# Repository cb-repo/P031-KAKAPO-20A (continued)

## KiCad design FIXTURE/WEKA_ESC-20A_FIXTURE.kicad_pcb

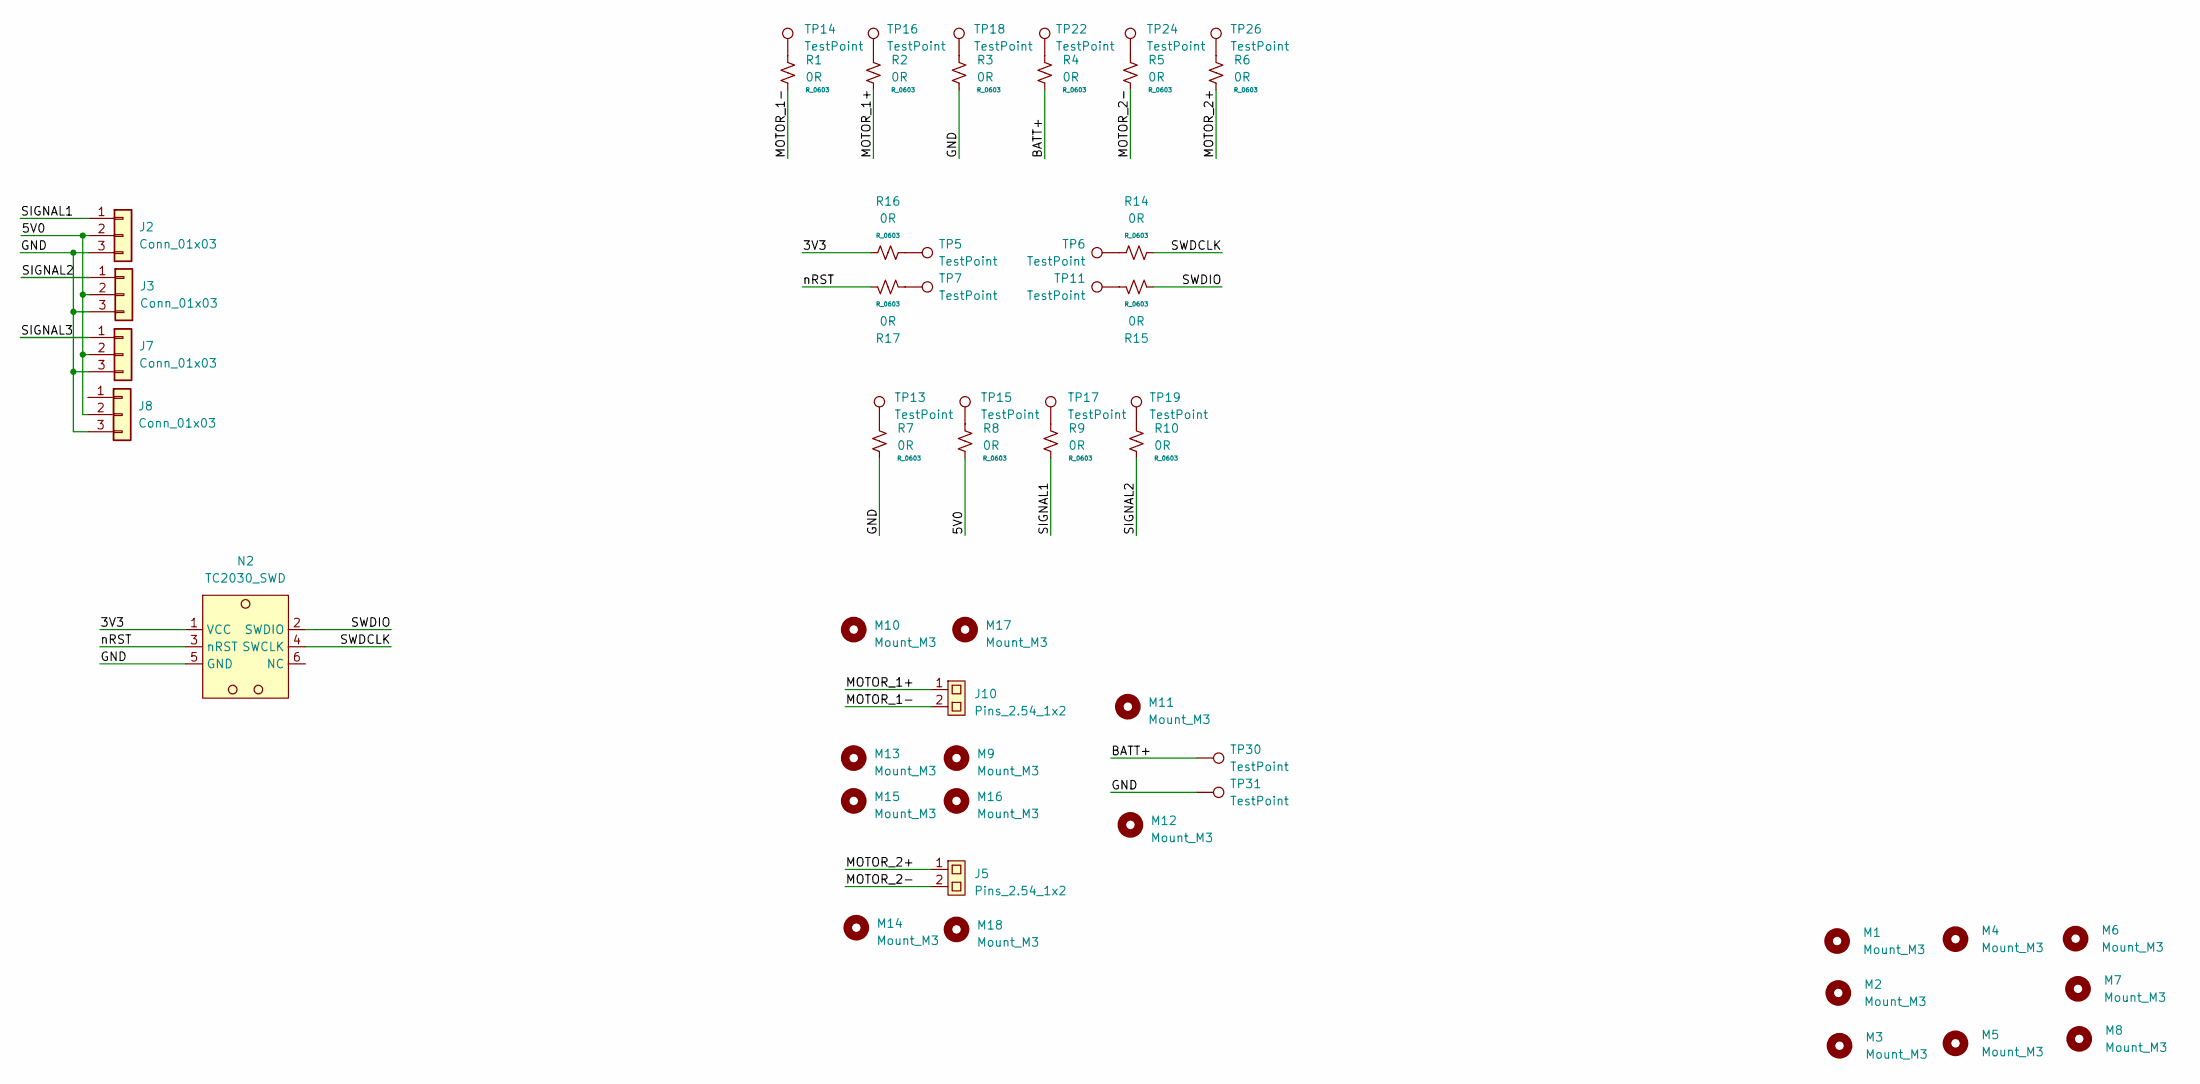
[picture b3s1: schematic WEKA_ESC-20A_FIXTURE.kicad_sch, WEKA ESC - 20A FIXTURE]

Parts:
J2, J3, J7, J8: Conn_01x03; PinHeader_1x03_P2.54mm_Vertical
J5, J10: Pins_2.54_1x2; Pins-2.54-1x2
M1, M2, M3, M4, M5, M6, M7, M8, M9, M10, M11, M12, M13, M14, M15, M16, M17, M18: Mount_M3
N2: TC2030_SWD; TagConnect_TC2030
R1, R2, R3, R4, R5, R6, R7, R8, R9, R10, R14, R15, R16, R17: 0R; R_0603
TP5, TP6, TP7, TP11, TP13, TP14, TP15, TP16, TP17, TP18, TP19, TP22, TP24, TP26, TP30, TP31: TestPoint; TestPoint_THTPad_D3.0mm_Drill1.5mm

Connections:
/3V3: N2.1 (VCC), R16.1
/5V0: J2.2, J3.2, J7.2, J8.2, R8.2
/BATT+: R4.2, TP30.1
/GND: J2.3, J3.3, J7.3, J8.3, N2.5 (GND), R3.2, R7.2, TP31.1
/MOTOR_1+: J10.1, R2.2
/MOTOR_1-: J10.2, R1.2
/MOTOR_2+: J5.1, R6.2
/MOTOR_2-: J5.2, R5.2
/SIGNAL1: J2.1, R9.2
/SIGNAL2: J3.1, R10.2
/SIGNAL3: J7.1
/SWDCLK: N2.4 (SWCLK), R14.2
/SWDIO: N2.2 (SWDIO), R15.2
/nRST: N2.3 (nRST), R17.1
unnamed: R1.1, TP14.1
unnamed: R2.1, TP16.1
unnamed: R3.1, TP18.1
unnamed: R4.1, TP22.1
unnamed: R5.1, TP24.1
unnamed: R6.1, TP26.1
unnamed: R7.1, TP13.1
unnamed: R8.1, TP15.1
unnamed: R9.1, TP17.1
unnamed: R10.1, TP19.1
unnamed: R14.1, TP6.1
unnamed: R15.1, TP11.1
unnamed: R16.2, TP5.1
unnamed: R17.2, TP7.1

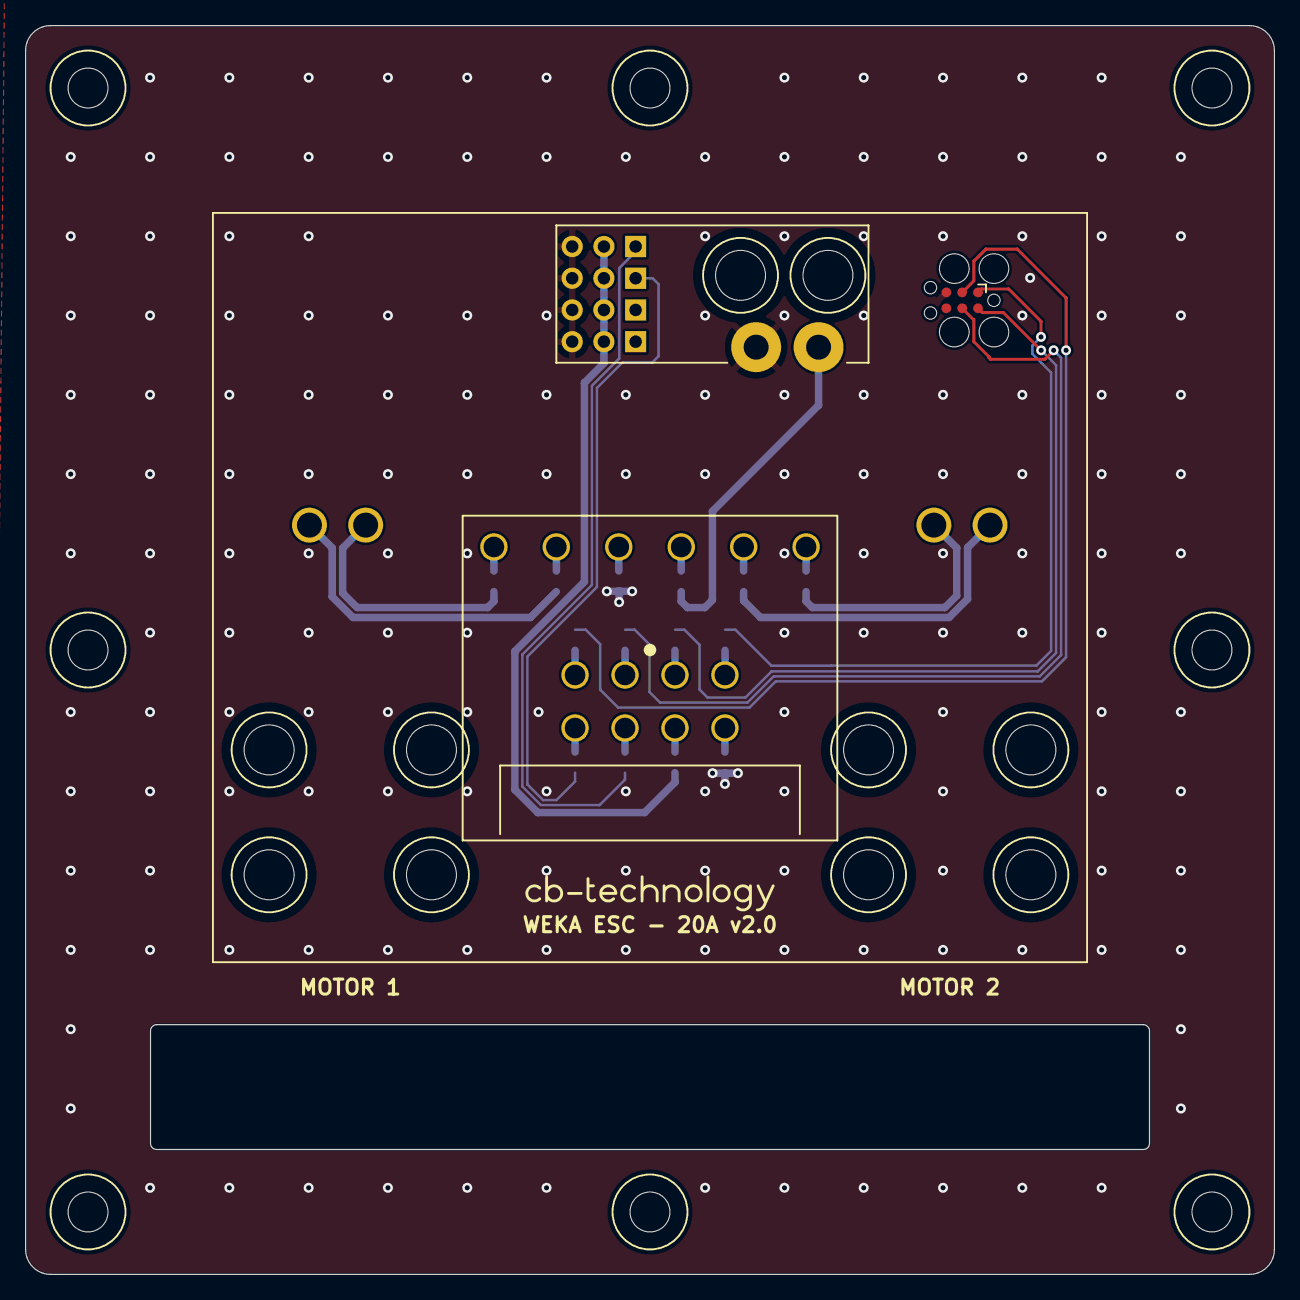
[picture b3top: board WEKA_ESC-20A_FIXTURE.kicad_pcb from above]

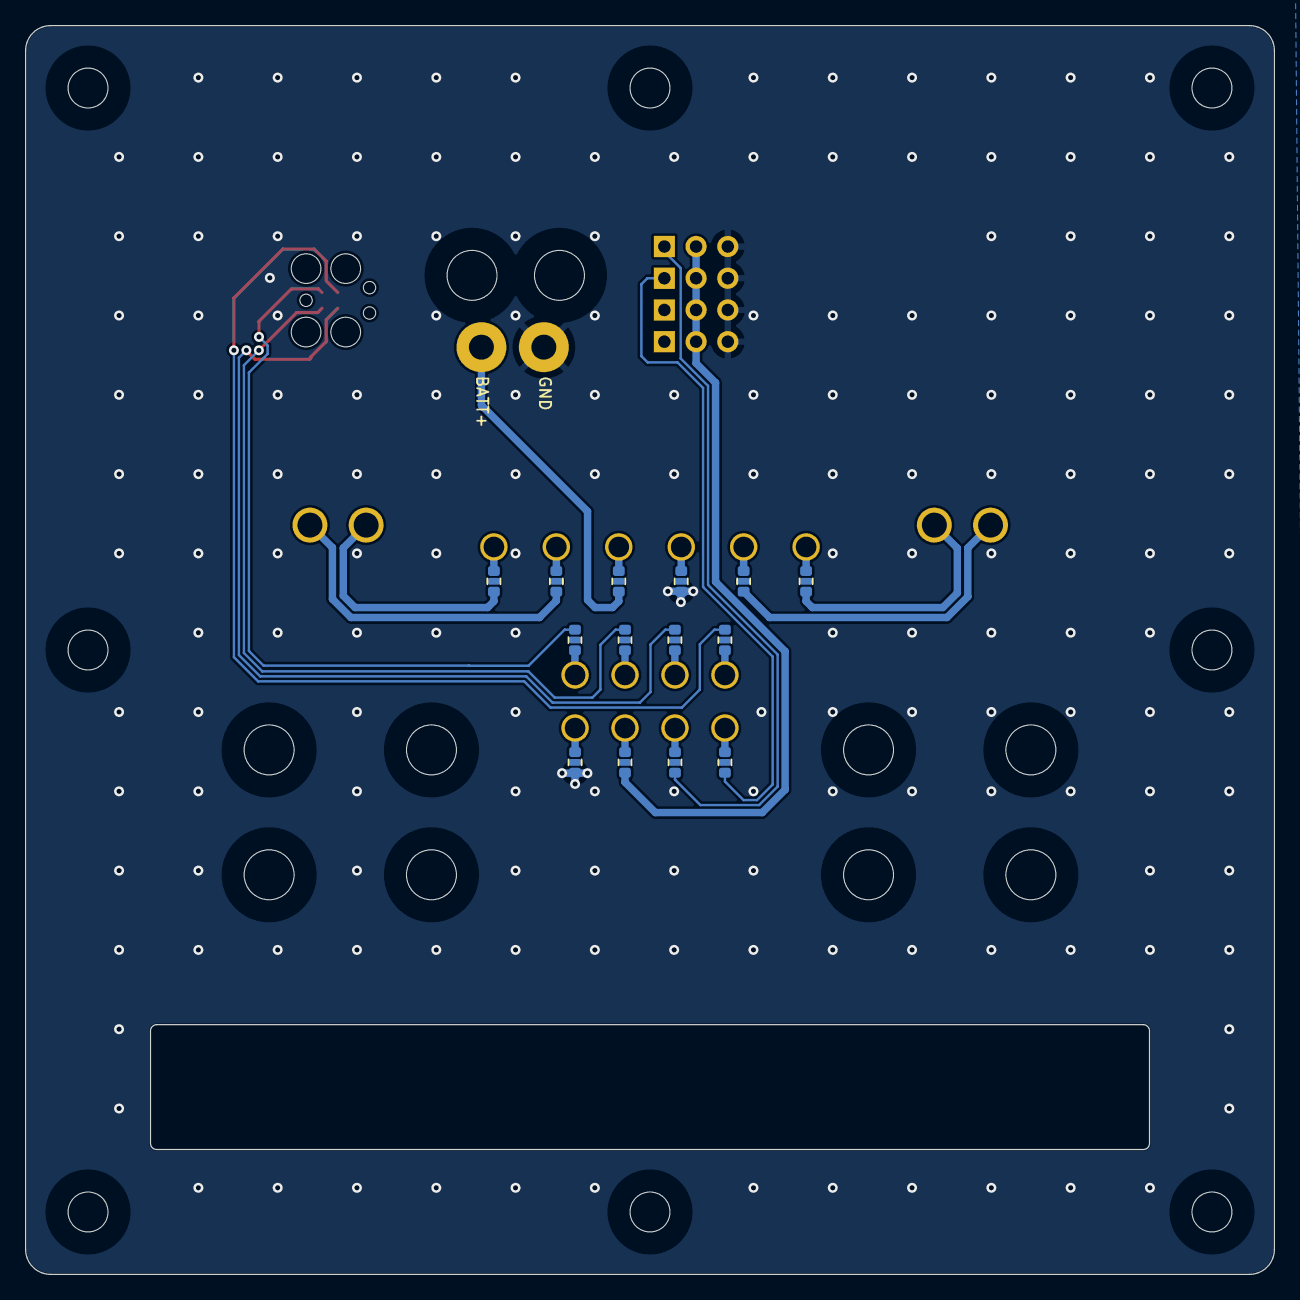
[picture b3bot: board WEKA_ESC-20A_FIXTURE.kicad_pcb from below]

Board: 2 copper layers, 100.0 x 100.0 mm, 55 parts (16 on the bottom side), 27 nets.

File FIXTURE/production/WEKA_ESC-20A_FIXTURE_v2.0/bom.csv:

Designator,Footprint,Quantity,Value,LCSC Part #
"J10, J5",Pins-2.54-1x2,2,Pins_2.54_1x2,
"J2, J3, J7, J8",PinHeader_1x03_P2.54mm_Vertical,4,Conn_01x03,
"R1, R10, R14, R15, R16, R17, R2, R3, R4, R5, R6, R7, R8, R9",R_0603,14,0R,
"TP11, TP13, TP14, TP15, TP16, TP17, TP18, TP19, TP22, TP24, TP26, TP30, TP31, TP5, TP6, TP7",TestPoint_THTPad_D3.0mm_Drill1.5mm,16,TestPoint,

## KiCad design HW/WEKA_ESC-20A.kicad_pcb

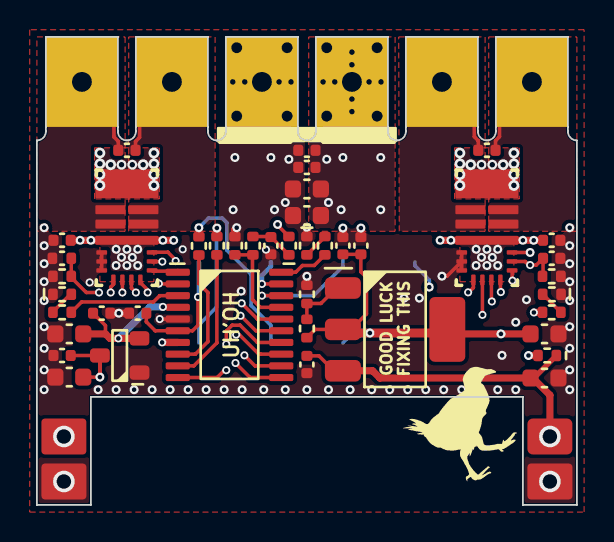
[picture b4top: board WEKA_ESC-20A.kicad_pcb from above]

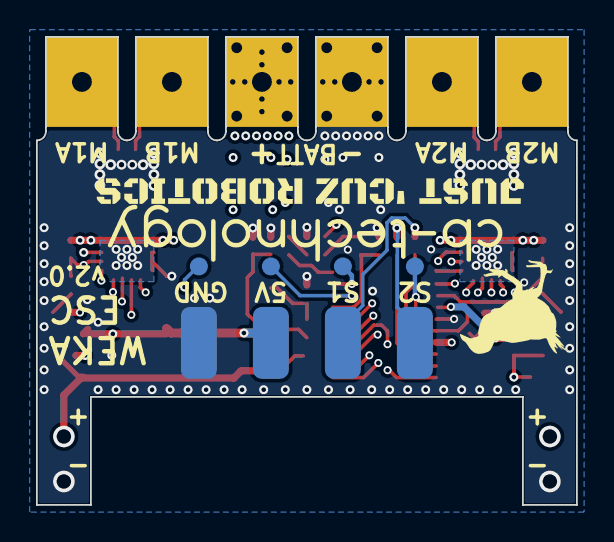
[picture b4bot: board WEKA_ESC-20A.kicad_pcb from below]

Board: 4 copper layers, 30.0 x 26.0 mm, 60 parts (13 on the bottom side), 34 nets.

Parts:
C1: 1uF 35V; C_0402
C2, C3, C4, C6, C7, C8, C10, C14, C19, C20, C23, C28, C29: 100nF 50V; C_0402
C5, C12, C15: 10uF 10V; C_0603
C9, C16, C17: 10uF 35V; C_0603
C11: 1uF 50V; C_0402
D1, D2: RB161QS-40T18R; R_0402
DS1, DS3: BLUE; DS_0402
DS2: RED; DS_0402
N1, N2, N3, N4: Pad_4x2
N5, N6, N7, N8: Pad_4x2_TH; Pad_4x2
N11, N12, N13, N14, N15, N16: Finger_4x5_M1
R1, R3: 619R 1%; R_0402
R2: 243 1%; R_0402
R6, R7: 1K 1%; R_0402
R10, R11, R12: 120R 1%; R_0402
R24: 100K 1%; R_0402
R25: 10K 1%; R_0402
R27: 732 1%; R_0402
TP1, TP2, TP3, TP4: TestPoint; TestPoint_Pad_D1.5mm
U1, U2: DRV8244S-Q1; VQFN-HR-16
U3: LR7533-T; SOT23_3
U4: LM317EMPX/NOPB; SOT223_3
U5: STM32C011F4P6; TSSOP20_4.4mm

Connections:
+3V3: C4.1, C5.1, TP1.1, U1.3 (nSLEEP), U2.3 (nSLEEP), U3.2 (VOUT), U5.4 (VDD/VDDA)
+5V: C1.1, C2.1, C10.1, C12.1, C15.1, N5.1, R2.1, U3.3 (VIN), U4.2 (VOUT)
/MCU/SWDCLK: TP4.1, U5.19 (PA14-BOOT0[SWDCLK])
/MCU/SWDIO: TP3.1, U5.18 (PA13[SWDIO])
/MCU/nRST: C14.1, TP2.1, U5.6 (PF2-NRST)
GND: C1.2, C2.2, C3.2, C4.2, C5.2, C6.2, C9.2, C10.2, C11.2, C12.2, C14.2, C15.2, C16.2, C17.2, C19.2, C20.2, C23.2, C28.2, C29.2, DS1.1 (K), DS2.1 (K), DS3.1 (K), N2.1, N4.1, N6.1, N12.1, R1.2, R3.2, R25.2, R27.2, U1.7 (GND), U1.10 (DRVOFF), U1.11 (EN/IN1), U1.12 (PH/IN2), U2.7 (GND), U2.10 (DRVOFF), U2.11 (EN/IN1), U2.12 (PH/IN2), U3.1 (GND), U5.5 (VSS/VSSA)
LED_M1: R11.1, U5.10 (PA3)
LED_M2: R12.1, U5.3 (PC15/OSCX_OUT)
LED_PWR: R10.1, U5.20 (PB6)
MOTOR_A+: C7.1, N13.1, U1.8 (OUT1), U1.9 (OUT1)
MOTOR_A-: C7.2, N14.1, U1.5 (OUT2), U1.6 (OUT2)
MOTOR_A_SNS: C28.1, R1.1, U1.2 (IPROPI), U5.11 (PA4)
MOTOR_A_nFAULT: U1.1 (nFAULT), U5.16 (PA11[PA9])
MOTOR_A_nSCS: U1.13 (nSCS), U5.15 (PA8)
MOTOR_B+: C8.1, N15.1, U2.8 (OUT1), U2.9 (OUT1)
MOTOR_B-: C8.2, N16.1, U2.5 (OUT2), U2.6 (OUT2)
MOTOR_B_SNS: C19.1, R3.1, U2.2 (IPROPI), U5.7 (PA0)
MOTOR_B_nFAULT: U2.1 (nFAULT), U5.1 (PB7)
MOTOR_B_nSCS: U2.13 (nSCS), U5.2 (PC14/OSCX_IN)
MOTOR_SCLK: U1.14 (SCLK), U2.14 (SCLK), U5.12 (PA5)
MOTOR_SDI: U1.15 (SDI), U2.15 (SDI), U5.14 (PA7)
MOTOR_SDO: U1.16 (SDO), U2.16 (SDO), U5.13 (PA6)
unnamed: C23.1, D2.1, R24.1
unnamed: DS1.2 (A), R12.2
unnamed: DS2.2 (A), R10.2
unnamed: DS3.2 (A), R11.2
unnamed: N7.1, R6.1
unnamed: N8.1, R7.1
unnamed: R2.2, R27.1, U4.1 (ADJ)
unnamed: C6.1, C9.1, D1.1, N1.1, U4.3 (VIN)
RADIO_CH1: R6.2, U5.8 (PA1)
RADIO_CH2: R7.2, U5.9 (PA2)
VCC: C3.1, C11.1, C16.1, C17.1, C20.1, C29.1, D1.2, D2.2, N3.1, N11.1, U1.4 (VM), U2.4 (VM)
V_BATT: R24.2, R25.1, U5.17 (PA12[PA10])

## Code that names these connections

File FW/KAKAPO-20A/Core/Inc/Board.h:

/* ~~~~~~~~~~~~~~~~~~~~~~~~~~~~~~~~~~~~~~~~~~~~~~~~~~~~ */
#ifndef BOARD_H
#define BOARD_H
/* ~~~~~~~~~~~~~~~~~~~~~~~~~~~~~~~~~~~~~~~~~~~~~~~~~~~~ */

/* ~~~~~~~~~~~~~~~~~~~~~~~~~~~~~~~~~~~~~~~~~~~~~~~~~~~~ */
/* PUBLIC DEFINITIONS									*/
/* ~~~~~~~~~~~~~~~~~~~~~~~~~~~~~~~~~~~~~~~~~~~~~~~~~~~~ */

#define STM32C0

//
#define RADIO_NUM_CHANNELS		4
#define SERVO_NUM_OUTPUTS		2

// CORE CONFIG
#define CORE_USE_TICK_IRQ

// FLASH CONFIG
#define FPROM_PAGE_SIZE 		256

// ADC CONFIG
#define ADC_VREF	       		3300

// CLK CONFIG
#define CLK_SYSCLK_FREQ			48000000

// TIMER CONFIG
#define TIM_USE_IRQS

// TIMER CONFIG - RADIO INPUT
#define TIM14_ENABLE
#define TIM_RADIO				TIM_14
#define TIM_RADIO_RELOAD		0xffff
#define TIM_RADIO_FREQ			1000000
#define PWM_TIM					TIM_RADIO
#define PWM_TIM_FREQ			TIM_RADIO_FREQ
#define PWM_TIM_RELOAD			TIM_RADIO_RELOAD
#define PPM_TIM					TIM_RADIO
#define PPM_TIM_FREQ			TIM_RADIO_FREQ
#define PPM_TIM_RELOAD			TIM_RADIO_RELOAD

// TIMER CONFIG - MOTOR OUTPUT
#define TIM1_ENABLE
#define TIM_MOTORA				TIM_1
#define TIM_MOTORA_CH			0
#define TIM_MOTOR_M2_CH			1
#define TIM_MOTORA_RELOAD		500
#define TIM_MOTORA_FREQ			130000 // 130000 //250000 //750000
#define TIM3_ENABLE
#define TIM_MOTORB				TIM_3
#define TIM_MOTORB_CH			0
#define TIM_MOTORB_RELOAD		TIM_MOTORA_RELOAD	// 500
#define TIM_MOTORB_FREQ			TIM_MOTORA_FREQ 		// (((TIM_MOTORB_RELOAD + 1) * 1000) / MOTOR_PERIOD_MS)

// TIMER CONFIG - SERVO OUTPUT
#if SERVO_NUM_OUTPUTS >= 1
#define TIM16_ENABLE
#define TIM_SERVO_S1			TIM_16
#define TIM_SERVO_S1_RELOAD		(10*1000)
#define TIM_SERVO_S1_FREQ		1000000
#if SERVO_NUM_OUTPUTS >= 2
#define TIM17_ENABLE
#define TIM_SERVO_S2			TIM_17
#define TIM_SERVO_S2_RELOAD		(10*1000)
#define TIM_SERVO_S2_FREQ		1000000
#endif
#endif

// SPI CONFIG - MOTOR OUTPUT
#define MOTOR_SPI_CLK			PB3
#define MOTOR_SPI_MOSI			PB5
#define MOTOR_SPI_MISO			PB4
#define MOTORA_Select			PB9
#define MOTORA_Fault			PB7
#define MOTORA_Sense			PA11
#define MOTORA_Sense_Ch			ADC_Channel_11
#define MOTORB_Select			PA15
#define MOTORB_Fault			PB6
#define MOTORB_Sense			PA12
#define MOTORB_Sense_Ch			ADC_Channel_12

#define SPI1_PINS		    	(MOTOR_SPI_CLK | MOTOR_SPI_MOSI | MOTOR_SPI_MISO)
#define SPI1_AF			    	GPIO_AF0_SPI1

// GPIO CONFIG
#define GPIO_USE_IRQS
#define GPIO_IRQ6_ENABLE
#define GPIO_IRQ8_ENABLE
#define GPIO_IRQ9_ENABLE
#define GPIO_IRQ10_ENABLE

// GPIO CONFIG - RADIO INPUTS
#if RADIO_NUM_CHANNELS >= 2
#define RADIO_PWM1_Pin			PA8
#define RADIO_PWM2_Pin			PA9
#if RADIO_NUM_CHANNELS >= 3
#define RADIO_PWM3_Pin			PC6
#if RADIO_NUM_CHANNELS >= 4
#define RADIO_PWM4_Pin			PA10
#endif
#endif
#else
#error "Minimum: x2 Radio Inputs Defined"
#endif

// GPIO CONFIG - SERVO OUTPUT
#if SERVO_NUM_OUTPUTS >= 1
#define SERVO_S1_Pin			PB1
#if SERVO_NUM_OUTPUTS >= 2
#define SERVO_S2_Pin			PB2
#endif
#endif

// GPIO CONFIG - LED OUTPUT
//#define LED_PWR_Pin			PB6
#define LED_M1_Pin				PA0
#define LED_M2_Pin				PB0

// GPIO CONFIG - BATTERY DETECT
#define BATT_Pin				PA1
#define BATT_Ch      			ADC_Channel_1
#define BATT_Rlow				10
#define BATT_Rhigh				100


/* ~~~~~~~~~~~~~~~~~~~~~~~~~~~~~~~~~~~~~~~~~~~~~~~~~~~~ */
/* PUBLIC TYPES      									*/
/* ~~~~~~~~~~~~~~~~~~~~~~~~~~~~~~~~~~~~~~~~~~~~~~~~~~~~ */

/* ~~~~~~~~~~~~~~~~~~~~~~~~~~~~~~~~~~~~~~~~~~~~~~~~~~~~ */
/* PUBLIC FUNCTIONS										*/
/* ~~~~~~~~~~~~~~~~~~~~~~~~~~~~~~~~~~~~~~~~~~~~~~~~~~~~ */

/* ~~~~~~~~~~~~~~~~~~~~~~~~~~~~~~~~~~~~~~~~~~~~~~~~~~~~ */
/* EXTERN DECLARATIONS									*/
/* ~~~~~~~~~~~~~~~~~~~~~~~~~~~~~~~~~~~~~~~~~~~~~~~~~~~~ */

/* ~~~~~~~~~~~~~~~~~~~~~~~~~~~~~~~~~~~~~~~~~~~~~~~~~~~~ */
#endif /* BOARD_H */
/* ~~~~~~~~~~~~~~~~~~~~~~~~~~~~~~~~~~~~~~~~~~~~~~~~~~~~ */

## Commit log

2024-02-29 Copy in WEKA-20A v2.0 HW as a starting point
2024-03-10 WIP - Layout XT30/PCB Finger Positions
2024-03-14 WIP - Layout Motor Drivers + Buck Circuit
2024-03-15 WIP - Continue Tracking MCU
2024-04-11 WIP - Final Detail Design Before Design Review
2024-04-19 Update .gitignore to remove KiCAD backup files
2024-04-24 Move 5V Supply Around To Make More Efficient Conduction Path
2024-04-27 Finish Tracking and Release For MFG
2024-04-28 Update Part Numbers For Second Release
2024-06-04 Remove WEKA Production Files
2024-06-04 Update gitignore
2024-06-04 Create Packaging Label
2024-06-15 Update Switch NPTH Geometry and VBatt Circuit
2024-06-16 Fix Motor Driver Comms Tracking Issue
2024-06-16 Update LED to Visible Wavelength
2024-06-17 Create Fixture PCB
2024-07-09 Create v1.0 Fixed From v0.2 HW
2024-07-17 Create FW Repo W/ Code From Latest WEKA-20A
2024-07-17 WIP FW Commit - Debugging SPI Non-Functionalty
2024-07-19 Get Motor Output Working and Implement Servo Outputs
2024-07-21 Code Base Running For Junkyard 2024 Competition
2024-07-21 Resolve 12V output restriction for Junkyard
2024-07-27 Build FW Output File For Junkyard Competition
2024-08-18 Start Outlining Price Breakdown
2024-09-12 WIP Commit
2024-11-09 Port updates from KAKAPO-2A Hash 8200f0
2025-01-29 Extend Calibration Timeout For Usability
2025-01-29 Update Fixture Design to Be Inline With Other Jigs
2025-05-19 Start Readme Files
2025-05-19 Update Readme Title
2025-06-09 Add Phonetic Spelling to Readme
